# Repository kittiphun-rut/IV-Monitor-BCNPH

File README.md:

# IV-Monitor-BCNPH

ซอฟต์แวร์ของโครงการนวัตกรรม **Smart IV Alert** — ระบบตรวจวัดและแจ้งเตือนการให้สารน้ำทางหลอดเลือดดำ
(หอผู้ป่วยอายุรกรรม โรงพยาบาลสูงเม่น จังหวัดแพร่ / วิทยาลัยพยาบาลบรมราชชนนี แพร่)

## โครงสร้างที่เก็บ

เฟิร์มแวร์เก็บเป็น **โฟลเดอร์ชื่อคงที่สายละหนึ่ง** เลขเวอร์ชันอยู่ใน `#define APP_VERSION`
เวอร์ชันเก่าทุกตัวดูได้จาก [`VERSIONS.md`](VERSIONS.md) ซึ่งมีลิงก์โหลด zip ของทุกรุ่น

| ที่อยู่ | คำอธิบาย |
|---|---|
| `firmware/Station/` | **เฟิร์มแวร์เครื่องประจำเตียง สายหลัก** — ไม่ต้องคาลิเบรตด้วยมือ หนีบเซนเซอร์แล้วเปิดโรลเลอร์ เครื่องเรียนรู้เอง หมุนจอ 180 องศาได้ สุ่มจังหวะส่งข้อมูลกันชนกัน |
| `firmware/Station-Stable/` | **เฟิร์มแวร์เครื่องประจำเตียง สายเสถียร** — อัลกอริทึมตรวจจับเดิมพร้อมหน้าคาลิเบรต ๓ ขั้นแบบทำเอง สำหรับเครื่องที่ยังใช้วิธีเดิม |
| `firmware/Host-OLED/` | **เฟิร์มแวร์เครื่องส่วนกลาง จอ OLED** — ตรวจเลขเตียงซ้ำ หน้า LINK DIAGNOSTIC แอนิเมชันหยด หน้าเว็บ Dashboard |
| `firmware/Host-TFT28/` | **เฟิร์มแวร์เครื่องส่วนกลาง จอสี TFT 2.8"** — หน้าจอแนวทาง FOCUS + จอเตือนเต็มจอ |
| `firmware/Host-Touch24/` | **เฟิร์มแวร์เครื่องส่วนกลาง จอสัมผัส 2.4"** — ตั้งค่าได้บนจอ นาฬิกา DS3231 บันทึกลงการ์ด SD พร้อมคุณสมบัติครบเท่ารุ่นจอ OLED |
| `firmware/FlowSim-Lab/` | **เฟิร์มแวร์แบบจำลองกราฟการไหล + ทดสอบเซนเซอร์** (ไม่เชื่อมต่อ Host) — ใช้ทดลอง สาธิต และออกแบบหน้าจอ |
| `firmware/reference/` | เฟิร์มแวร์ตัวจริงที่ใช้อ้างอิง: Station v7.3.0 / v7.4.0 และ Host v4.6.0 |
| `tools/check-ino-types.py` | ตรวจว่า enum/struct ถูกประกาศก่อนจุดที่ Arduino แทรก prototype (กัน error `does not name a type`) |
| `tools/screen-preview/` | เครื่องมือเรนเดอร์ภาพหน้าจอ TFT จากไฟล์ .ino บนเครื่อง PC |
| `tools/touch-preview/` | เรนเดอร์ภาพหน้าจอของเฟิร์มแวร์ Host จอสัมผัส v4.9.0 บน PC |
| `tools/host-preview/` | เรนเดอร์ภาพหน้าจอ TFT ของเฟิร์มแวร์ Host v4.8.0-TFT บน PC |
| `tools/protocol-test/` | **ตรวจว่าโครงสร้างแพ็กเก็ต ESP-NOW ของทุกเฟิร์มแวร์ตรงกัน** (Host กับ Station ต้องตรงกันทุกไบต์) |
| `tools/oled-check/` | ตรวจว่าเฟิร์มแวร์ Host จอ OLED คอมไพล์ผ่านบน PC |
| `tools/oled-preview/` | **จำลองหน้าจอ OLED 128x64 ของ Host v4.7.4 บน PC** เรนเดอร์ออกมาเป็นภาพทุกหน้า รวมเฟรมแอนิเมชันหยด |
| `tools/host-rx-test/` | **ป้อนแพ็กเก็ตเสมือนเข้าฟังก์ชันรับของ Host บน PC** ตรวจว่า Host มองเห็นครบทุกเตียงจริงหรือไม่ (7 สถานการณ์ รวมกรณีเลขเตียงซ้ำ) |
| `tools/link-sim/` | **จำลองจังหวะเวลาของ ESP-NOW ทั้งระบบ** วัดว่าของเดิมทำให้ Host ขึ้น OFFLINE ผิดพลาดนานเท่าใด และของใหม่แก้ได้แค่ไหน |
| `tools/dashboard-preview/` | **เปิดหน้าเว็บ Dashboard บน PC พร้อมข้อมูลจำลอง** แล้วถ่ายภาพหน้าจอด้วย Chromium |
| `tools/detector-test/` | **ทดสอบอัลกอริทึมตรวจจับหยดบน PC** 10 สถานการณ์ (ถุงแกว่ง ระดับไหล สัญญาณรบกวนแรง ฯลฯ) ไม่ต้องมีบอร์ด |
| `tools/station-preview/` | เรนเดอร์ภาพทุกหน้าจอของเฟิร์มแวร์ Station v7.7.2 บน PC (มีเซนเซอร์จำลองในตัว) |
| `tools/ui-mockup/` | แบบร่าง UI ของจอ Station 3 แนวทาง (เรนเดอร์เป็นภาพเพื่อเลือกแบบก่อนลงมือเขียนจริง) |
| `hardware/` | **ผังการเชื่อมต่ออุปกรณ์ KiCad 7** ของเครื่องประจำเตียงและเครื่องศูนย์กลาง สร้างจากหมายเลขขาในเฟิร์มแวร์โดยอัตโนมัติ พร้อมสคริปต์ตรวจว่าผังตรงกับโค้ด |
| `docs/screens/` | ภาพตัวอย่างหน้าจอที่สร้างจากเครื่องมือข้างต้น |
| `docs/ui-concepts/` | ภาพเปรียบเทียบแบบร่าง UI ทั้ง 3 แนวทาง |
| `docs/screens-touch/` | ภาพหน้าจอจริงของ Host v4.9.1-TOUCH ทุกหน้า |
| `docs/ui-concepts-touch/` | แบบร่าง UI แบบสมาร์ตโฟนที่ใช้ประกอบการเลือก |
| `docs/screens-host/` | ภาพหน้าจอจริงของ Host v4.8.0-TFT ทุกหน้า |
| `docs/ui-concepts-host/` | ภาพเปรียบเทียบแบบร่าง UI ของ Host ทั้ง 3 แนวทาง |
| `docs/screens-dashboard/` | ภาพหน้าเว็บ Dashboard ที่เรนเดอร์จากเบราว์เซอร์จริง |
| `docs/screens-station/` | ภาพหน้าจอจริงของ Station v7.7.2 ทุกหน้า + ภาพเปรียบเทียบจอหมุน 180 องศา |
| `docs/คู่มือพยาบาล_Smart_IV_Alert.docx` | **คู่มือการปฏิบัติงานสำหรับพยาบาลวิชาชีพ** ตามรูปแบบเอกสารราชการไทย ๔๘ หน้า (ปก คำนำ สารบัญ ๗ บท ภาคผนวก ๕ ภาค รวมบทการติดตั้งเซนเซอร์และการคาลิเบรต) — สารบัญเป็นฟิลด์ TOC ที่อัปเดตเองได้ใน Word |
| `docs/คู่มือหน้าเว็บ_Smart_IV_Alert.docx` | **คู่มือการปฏิบัติงานเฉพาะหน้าเว็บ** ๓๐ หน้า อธิบายทุกหน้า ทุกปุ่ม และทุกบรรทัดบนการ์ดเตียง พร้อมภาพถ่ายหน้าจอจริงทั้ง ๔ หน้า |
| `docs/คู่มือพยาบาล_Smart_IV_Alert.txt` | คู่มือฉบับข้อความล้วน สำหรับคัดลอกไปใช้ต่อหรืออ่านโดยไม่ต้องมี Word |
| `docs/คู่มือพยาบาล_Smart_IV_Alert_ตัวอย่าง.pdf` | ตัวอย่าง PDF ของคู่มือ (เรนเดอร์ด้วยฟอนต์แทน ไม่ใช่ TH SarabunPSK) |
| `tools/manual-build/` | **สคริปต์สร้างคู่มือ .docx** สร้างสารบัญเป็นฟิลด์ TOC จริงพร้อมเลขหน้าที่คำนวณไว้ล่วงหน้า |
| `docs/screens-oled/` | ภาพจำลองหน้าจอ OLED ของ Host v4.7.4-OLED ทุกหน้า + เฟรมแอนิเมชันหยด |

## เริ่มต้นที่ไหน

อ่าน [`firmware/FlowSim-Lab/README.md`](firmware/FlowSim-Lab/README.md)
ซึ่งอธิบายผังหน้าจอทั้ง 3 หน้า ตารางปุ่มกด โหมดจำลอง และขั้นตอนคาลิเบรตไว้ครบ

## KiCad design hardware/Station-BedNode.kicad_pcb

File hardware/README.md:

# ผังการเชื่อมต่ออุปกรณ์ (KiCad)

ผังในโฟลเดอร์นี้สร้างด้วย `tools/kicad-gen/gen_schematics.py` ซึ่ง **อ่านหมายเลขขา
GPIO จากไฟล์เฟิร์มแวร์โดยตรง ไม่ได้กรอกด้วยมือ** ถ้าย้ายขาในเฟิร์มแวร์แล้วรันสคริปต์ใหม่
ผังจะตามไปเองทันที ผังกับโค้ดจึงไม่มีทางหลุดจากกัน

```bash
python3 tools/kicad-gen/gen_schematics.py
```

| ไฟล์ | บอร์ด | อ่านขาจาก |
|---|---|---|
| `Station-BedNode.kicad_sch` | เครื่องประจำเตียง v7.7.3 | `firmware/Station/` |
| `Host-OLED.kicad_sch` | เครื่องศูนย์กลาง v4.7.5-OLED | `firmware/Host-OLED/` |

เปิดด้วย KiCad 7 ขึ้นไป (ไฟล์ `.kicad_pro` มีให้แล้ว) นิยามสัญลักษณ์ทั้งหมดฝังอยู่ในไฟล์
จึงเปิดได้บนเครื่องที่ไม่ได้ติดตั้งไลบรารีมาตรฐานของ KiCad

## ทำไมข้อความในผังเป็นภาษาอังกฤษ

KiCad 7 **ไม่รองรับการจัดวางสระและวรรณยุกต์ไทย** ทดสอบแล้วพบว่าเครื่องหมายบนและล่าง
หายทั้งหมด เช่น "อัตราการไหล" เรนเดอร์ออกมาเป็น "อตราการไหล" และ "ผู้ป่วย" เป็น "ผปวย"
ถ้าใส่ภาษาไทยลงไปจะได้เอกสารที่อ่านผิดความหมาย จึงใช้ภาษาอังกฤษในผัง (เป็นธรรมเนียม
ของงาน EDA อยู่แล้ว) และอธิบายภาษาไทยไว้ในไฟล์นี้แทน

## เครื่องประจำเตียง (Station v7.7.3)

| อุปกรณ์ | ขา ESP32-S3 | หมายเหตุ |
|---|---|---|
| จอ TFT ST7789 1.47" — SCLK | GPIO 13 | |
| จอ TFT — MOSI (SDA) | GPIO 12 | |
| จอ TFT — RST | GPIO 11 | |
| จอ TFT — DC | GPIO 10 | |
| จอ TFT — CS | GPIO 9 | |
| จอ TFT — BLK (ไฟหน้าจอ) | GPIO 8 | |
| เซนเซอร์ TCRT5000 — AO | GPIO 4 | ขา DO ไม่ได้ใช้ |
| บัซเซอร์ | GPIO 3 | ชนิด Passive ขับด้วย `tone()` |
| ปุ่มผู้ใช้ | GPIO 2 | ต่อลง GND ได้เลย |
| RGB LED (WS2812) | GPIO 48 | **อยู่บนบอร์ดแล้ว ไม่ต้องต่อเพิ่ม** |

**ข้อควรระวัง**

1. จ่ายไฟจอและเซนเซอร์ด้วย **3V3 เท่านั้น** ขา GPIO ของ ESP32-S3 ทนได้ 3.3V การต่อ 5V
   เข้าขาสัญญาณจะทำให้ชิปเสียหาย
2. ปุ่มใช้ `pinMode(INPUT_PULLUP)` จึงต่อระหว่าง GPIO กับ GND ได้เลย ไม่ต้องมีตัวต้านทาน
   พูลอัปภายนอก
3. บัซเซอร์ที่ใช้ต้องเป็นชนิด **Passive** เพราะเฟิร์มแวร์สร้างความถี่เองด้วย `tone()`
   ถ้าใช้บัซเซอร์แบบแม่เหล็กซึ่งกินกระแสสูง ให้เพิ่มทรานซิสเตอร์ NPN ขับ อย่าต่อตรงกับ GPIO
4. วงจรวัดแบตเตอรี่ฝั่ง Station **ปิดอยู่ในเฟิร์มแวร์** (`STATION_BAT_ADC_PIN = -1`)
   ผังจึงไม่ได้วาดไว้ ถ้าจะเปิดใช้ ต้องแก้ค่านี้เป็นหมายเลขขา ADC แล้วต่อตัวแบ่งแรงดัน 1:1

## เครื่องศูนย์กลาง (Host v4.7.5-OLED)

| อุปกรณ์ | ขา ESP32-S3 | หมายเหตุ |
|---|---|---|
| จอ OLED SH1106 — SDA | GPIO 8 | I2C 400 kHz |
| จอ OLED SH1106 — SCL | GPIO 9 | |
| ปุ่มเปิด-ปิด / พักเสียงเตือน | GPIO 4 | **ต้องเป็น RTC GPIO (0-21)** |
| ปุ่มเปลี่ยนหน้าจอ | GPIO 5 | |
| บัซเซอร์ | GPIO 7 | ชนิด Passive |
| วัดแรงดันแบตเตอรี่ | GPIO 1 | ผ่านตัวแบ่งแรงดัน 1:1 |

**ข้อควรระวัง**

1. ปุ่มเปิด-ปิดต้องอยู่บนขา RTC GPIO เพราะใช้ปลุกเครื่องจาก deep sleep ด้วย `ext0`
   ที่ระดับลอจิก 0 ถ้าย้ายไปขาอื่นที่ไม่ใช่ RTC GPIO เครื่องจะปลุกไม่ขึ้น
2. **R1 กับ R2 ต้องมีค่าเท่ากัน** เฟิร์มแวร์คำนวณ `(raw / 4095) × 3.3 × 2.0`
   ซึ่งตรึงอัตราส่วนไว้ที่ 1:1 แล้ว ถ้าใช้ค่าต่างกันค่าที่อ่านได้จะผิด
   แบตเตอรี่เต็มที่ 4.2V ผ่านตัวแบ่งเหลือ 2.1V ยังอยู่ในช่วงที่ ADC รับได้
3. โมดูล OLED สำเร็จรูปส่วนใหญ่มีตัวต้านทานพูลอัป I2C มาแล้ว ถ้าโมดูลที่ใช้ไม่มี
   ให้เพิ่ม 4.7kΩ จาก SDA ขึ้น 3V3 และ 4.7kΩ จาก SCL ขึ้น 3V3
4. บัสวิ่งที่ 400 kHz ตามสเปก SH1106 ควรให้สายสั้นที่สุดเท่าที่ทำได้

## การตรวจสอบ

ผังทั้งสองผ่านการตรวจด้วย `kicad-cli` เวอร์ชัน 7.0.11 โดยตรวจสองชั้น

1. **เปิดไฟล์ได้จริง** — `kicad-cli sch export pdf` สร้าง PDF สำเร็จทั้งสองไฟล์
2. **การเชื่อมต่อถูกต้อง** — `kicad-cli sch export netlist` แล้วตรวจทุกเน็ตทีละเส้น
   ว่าตรงกับ `#define` ในเฟิร์มแวร์

```bash
kicad-cli sch export pdf     --output Station-BedNode.pdf Station-BedNode.kicad_sch
kicad-cli sch export netlist --output Station-BedNode.net Station-BedNode.kicad_sch
```

## ขอบเขตที่ยังไม่ได้ทำ

* **ยังไม่มีการวางลายวงจร (PCB layout)** ผังนี้เป็นผังการเชื่อมต่ออุปกรณ์ สำหรับต่อสาย
  ระหว่างโมดูลสำเร็จรูปหรือบัดกรีบนเพอร์ฟบอร์ด ยังไม่ได้ออกแบบแผ่นวงจรพิมพ์
* **ยังไม่ได้ประกอบและทดสอบกับฮาร์ดแวร์จริง** ผังสร้างจากการอ่านโค้ด ควรตรวจทานกับ
  ซิลค์สกรีนบนบอร์ดจริงอีกครั้งก่อนบัดกรี
* **ยังไม่มีผังของ Host รุ่นจอ TFT (v4.8.0) และรุ่นจอสัมผัส (v4.9.0)** ทั้งสองรุ่นใช้ผังขา
  ต่างจากรุ่น OLED

---

# แผ่นวงจรพิมพ์ (PCB)

เป็น **บอร์ดรอง (carrier board)** สองชั้น รูทะลุทั้งหมด ไม่มีชิ้นส่วน SMD
โมดูลสำเร็จรูปทุกตัวเสียบลงหัวต่อ จึงบัดกรีด้วยมือได้และถอดเปลี่ยนโมดูลที่เสียได้

```bash
python3 tools/kicad-gen/gen_pcb.py     # สร้างบอร์ดใหม่จากหมายเลขขาในเฟิร์มแวร์
bash hardware/verify_pcb.sh            # รัน DRC จริงแล้วรายงานเฉพาะระดับ error
```

| ไฟล์ | คือ |
|---|---|
| `Station-BedNode.kicad_pcb` | บอร์ดเครื่องประจำเตียง ขนาด ๑๐๐ x ๘๖ มม. |
| `Host-OLED.kicad_pcb` | บอร์ดเครื่องศูนย์กลาง ขนาด ๑๐๐ x ๘๖ มม. |
| `ModuleFitCheck.kicad_pcb` / `.pdf` | **แผ่นทดสอบขนาดโมดูล ๑:๑** |
| `gerbers/<board>/` | ไฟล์สั่งผลิต Gerber + Excellon drill |
| `<board>-PCB.pdf` | ภาพบอร์ดสำหรับดูและตรวจทาน |

## ⚠ ต้องทำก่อนสั่งผลิต — ตรวจขนาดโมดูลด้วยแผ่น ๑:๑

บอร์ด ESP32-S3 Super Mini เป็นบอร์ดที่ผู้ผลิตแต่ละเจ้าทำไม่เหมือนกัน ทั้ง **จำนวนขาต่อแถว
ระยะห่างระหว่างสองแถว และลำดับว่าขาไหนคือ GPIO อะไร** ค่าที่ใช้อยู่ตอนนี้เป็นค่าตั้งต้น
ที่ **ยังไม่ได้ยืนยันกับบอร์ดจริง** ถ้าไม่ตรง บอร์ดที่สั่งมาจะเสียบโมดูลไม่ลงและใช้ไม่ได้เลย

ขั้นตอนตรวจ

1. พิมพ์ `ModuleFitCheck.pdf` โดยตั้งค่าเครื่องพิมพ์เป็น **สเกล ๑๐๐% หรือ Actual size**
   ห้ามใช้ Fit to page
2. **วัดแถบ ๑๐ มม. บนกระดาษด้วยไม้บรรทัดก่อน** ถ้าไม่ได้ ๑๐ มม. พอดี แปลว่าตั้งค่าพิมพ์ผิด
   อย่าเพิ่งใช้แผ่นนี้ตัดสิน
3. วางบอร์ด ESP32-S3 Super Mini ตัวจริงทาบลงบนรอยขาสองแถว ขาต้องลงรูพอดีทุกขา
4. เทียบชื่อ GPIO ที่พิมพ์ไว้กับซิลค์สกรีนบนโมดูลจริงทีละขา
5. ถ้าไม่ตรง ให้แก้ `MODULE` ที่หัวไฟล์ `tools/kicad-gen/gen_pcb.py` แล้วรันใหม่

```python
MODULE = dict(
    rows=8,                 # จำนวนขาต่อหนึ่งแถว
    row_pitch=15.24,        # ระยะห่างระหว่างสองแถว (มม.)
    pin_pitch=2.54,         # ระยะห่างระหว่างขาในแถวเดียวกัน (มม.)
    left=['5V', 'GND', '3V3', 'GPIO13', 'GPIO12', 'GPIO11', 'GPIO10', 'GPIO9'],
    right=['GPIO8', 'GPIO7', 'GPIO6', 'GPIO5', 'GPIO4', 'GPIO3', 'GPIO2', 'GPIO1'],
)
MODULE_VERIFIED = False     # ตั้งเป็น True เมื่อตรวจกับบอร์ดจริงแล้ว
```

ตราบใดที่ `MODULE_VERIFIED` ยังเป็น `False` บอร์ดจะพิมพ์คำเตือน
`MODULE FOOTPRINT UNVERIFIED` ไว้บนซิลค์สกรีน เพื่อกันการสั่งผลิตโดยยังไม่ได้ตรวจ

## วิธีเดินลายที่ใช้

เดินแบบ **แมนฮัตตันสองชั้น** — `F.Cu` เดินเฉพาะแนวตั้ง `B.Cu` เดินเฉพาะแนวนอน ต่อกันด้วยเวีย
ตัวสร้างบังคับเงื่อนไขสามข้อด้วยโค้ดก่อนเดินสายทุกครั้ง ถ้าข้อใดไม่ผ่านจะหยุดทันที

1. ขาที่ต้องเดินสายทุกขาบนฝั่งเดียวกันต้องห่างกันในแนว y อย่างน้อย ๑.๐ มม.
2. ทุกเส้นได้คอลัมน์ x ของตัวเอง
3. คอลัมน์ต้องอยู่ในช่องเดินสายที่ไม่มีขาอุปกรณ์

เมื่อครบสามข้อ ลายจะไม่มีทางทับกันเลยโดยโครงสร้าง ไม่ต้องพึ่งการตรวจด้วยสายตา

ลายกว้าง ๐.๔ มม. ระยะห่าง ๐.๒๕ มม. เวีย ๐.๘ มม. เจาะ ๐.๔ มม.
ค่าเหล่านี้อยู่ในเกณฑ์ที่โรงงาน PCB ราคาประหยัดทุกเจ้ารับผลิตได้

## ผลตรวจ

รัน DRC จริงผ่าน `pcbnew.WriteDRCReport()` ของ KiCad 7.0.11

| บอร์ด | error | unconnected pads | warning |
|---|---|---|---|
| Station-BedNode | **๐** | **๐** | ๑๗ |
| Host-OLED | **๐** | **๐** | ๑๙ |

warning ที่เหลือเป็นเรื่องซิลค์สกรีนซ้อนทับกันเล็กน้อย และ `lib_footprint_issues`
ซึ่งเกิดจากการโหลด footprint จากพาธไฟล์โดยตรงแทนที่จะผ่านตารางไลบรารี ทั้งสองอย่าง
ไม่กระทบการผลิตและไม่กระทบการทำงานทางไฟฟ้า

## ขอบเขตที่ยังไม่ได้ทำ

* **ยังไม่ได้สั่งผลิตและยังไม่ได้ประกอบจริง** ทุกอย่างตรวจด้วยเครื่องมือบนเครื่องเท่านั้น
* **ขนาดและผังขาของโมดูล ESP32-S3 Super Mini ยังไม่ได้ยืนยัน** ดูหัวข้อด้านบน
* ยังไม่ได้ออกแบบกล่อง ตำแหน่งรูยึด M3 ทั้งสี่มุมกำหนดไว้ห่างขอบ ๔ มม.
  ควรตรวจกับกล่องจริงก่อน
* ยังไม่มีบอร์ดของ Host รุ่นจอ TFT v4.8.0 และรุ่นจอสัมผัส v4.9.0

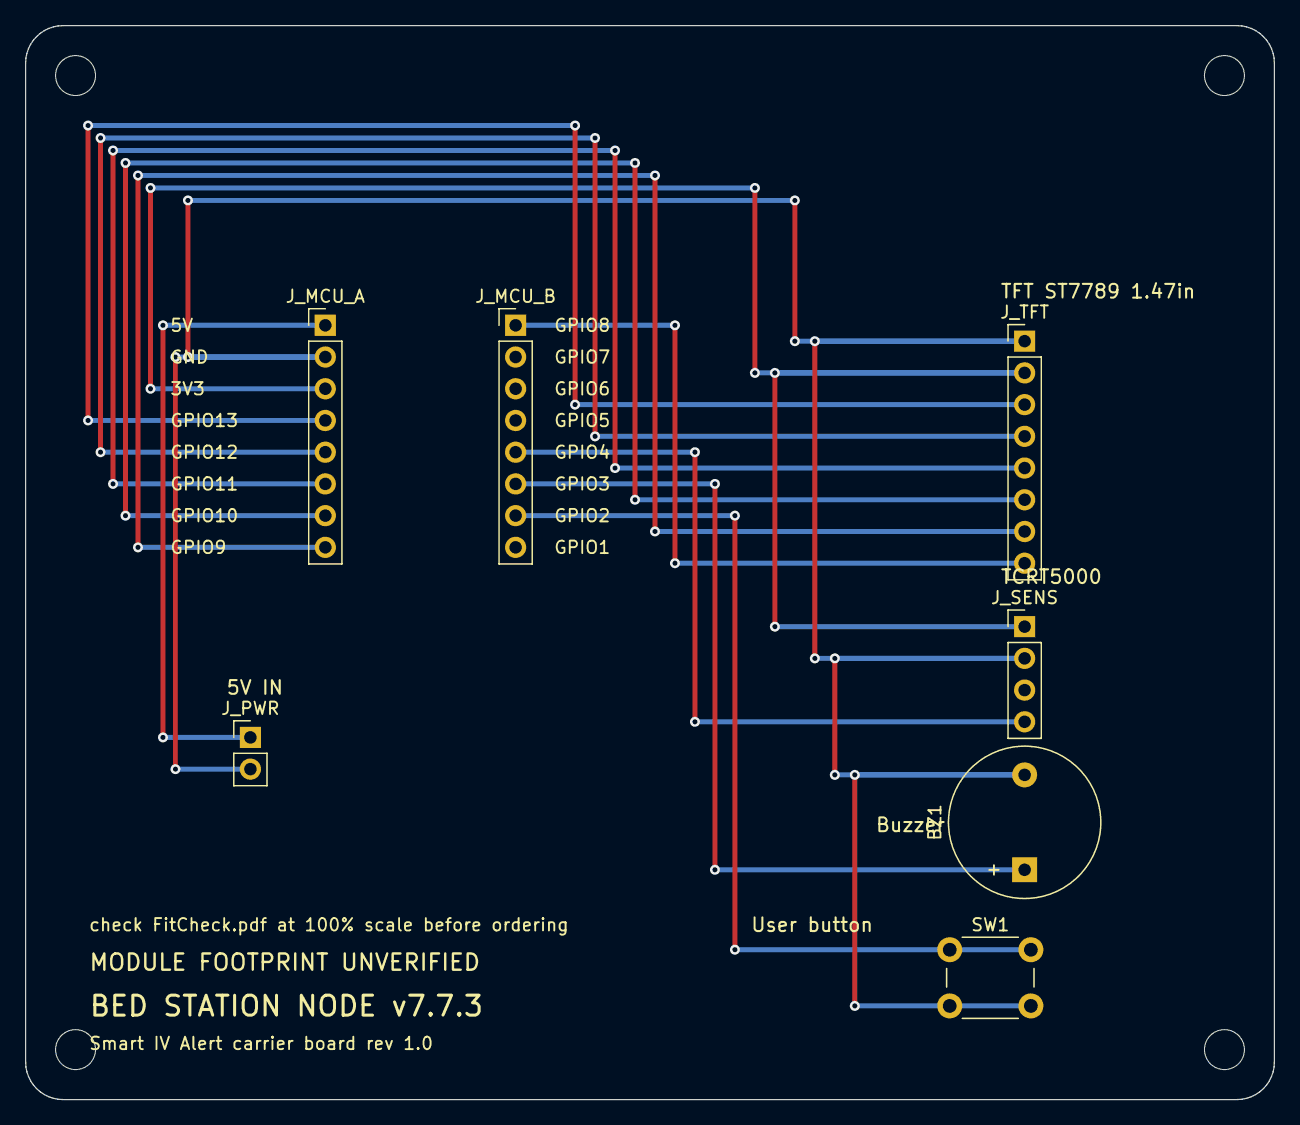
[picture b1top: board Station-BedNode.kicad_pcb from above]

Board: 2 copper layers, 100.0 x 86.0 mm, 11 parts (0 on the bottom side), 12 nets.

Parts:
BZ1: Buzzer; Buzzer_12x9.5RM7.6
H1, H2, H3, H4: MountingHole_3.2mm_M3
J_MCU_A: ESP32-S3 row A; PinHeader_1x08_P2.54mm_Vertical
J_MCU_B: ESP32-S3 row B; PinHeader_1x08_P2.54mm_Vertical
J_PWR: 5V IN; PinHeader_1x02_P2.54mm_Vertical
J_SENS: TCRT5000; PinHeader_1x04_P2.54mm_Vertical
J_TFT: TFT ST7789 1.47in; PinHeader_1x08_P2.54mm_Vertical
SW1: User button; SW_PUSH_6mm

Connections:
+3V3: J_MCU_A.3, J_SENS.1, J_TFT.2
+5V: J_MCU_A.1, J_PWR.1
BTN: J_MCU_B.7, SW1.1
BUZZER: BZ1.1, J_MCU_B.6
DROP_AO: J_MCU_B.5, J_SENS.4
GND: BZ1.2, J_MCU_A.2, J_PWR.2, J_SENS.2, J_TFT.1, SW1.2
TFT_BLK: J_MCU_B.1, J_TFT.8
TFT_CS: J_MCU_A.8, J_TFT.7
TFT_DC: J_MCU_A.7, J_TFT.6
TFT_MOSI: J_MCU_A.5, J_TFT.4
TFT_RST: J_MCU_A.6, J_TFT.5
TFT_SCLK: J_MCU_A.4, J_TFT.3

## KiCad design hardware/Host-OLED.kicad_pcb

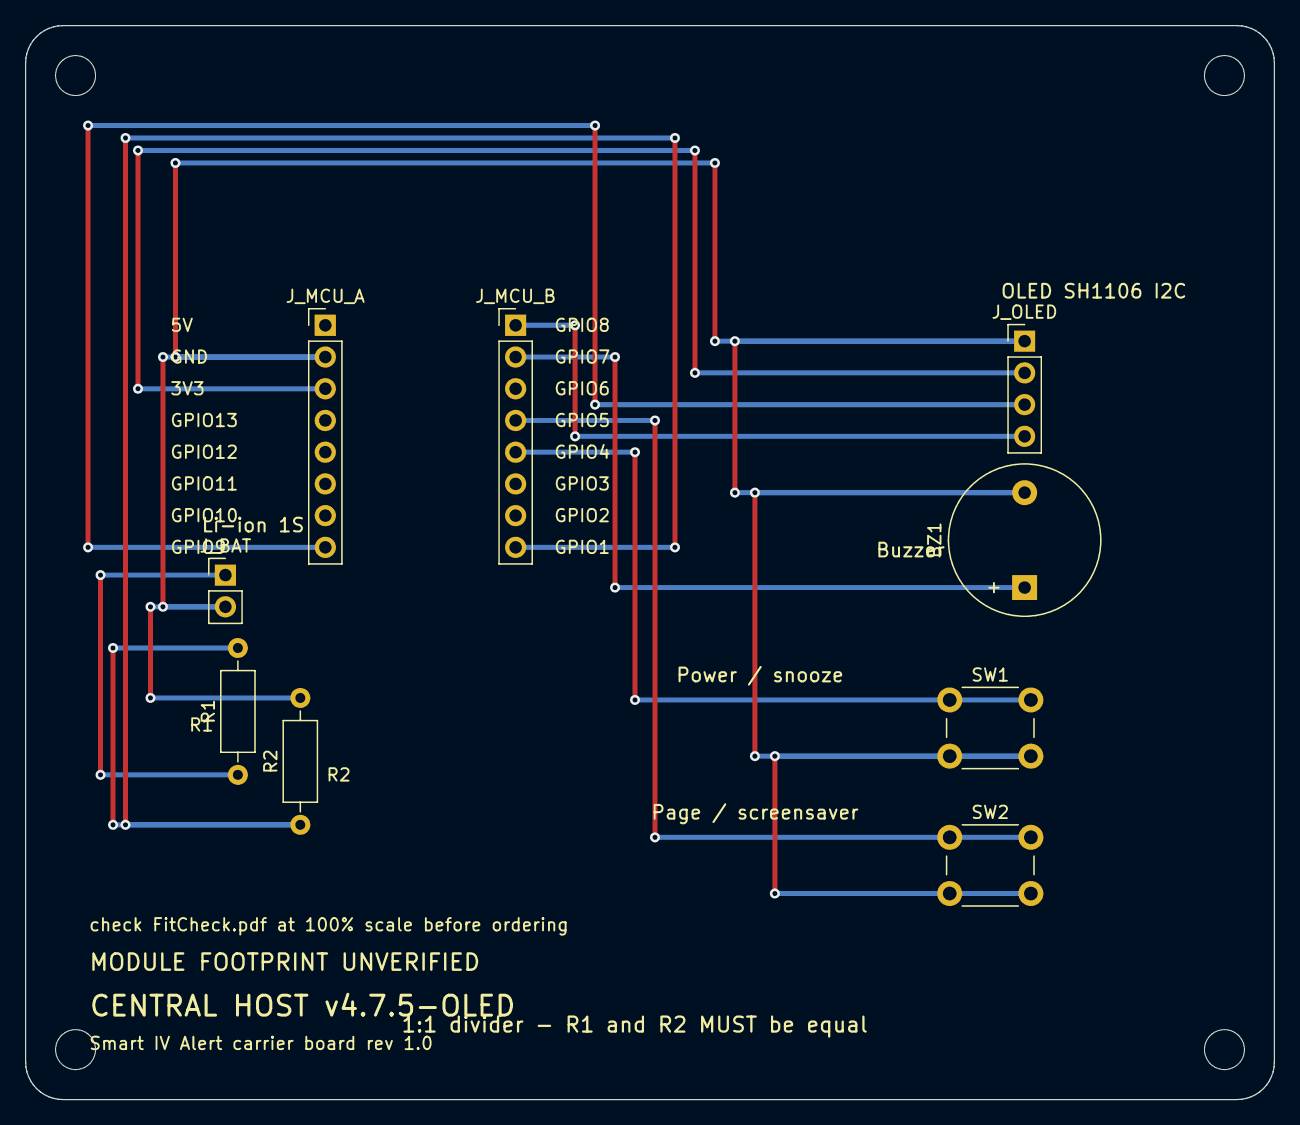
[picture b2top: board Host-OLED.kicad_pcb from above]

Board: 2 copper layers, 100.0 x 86.0 mm, 13 parts (0 on the bottom side), 9 nets.

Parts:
BZ1: Buzzer; Buzzer_12x9.5RM7.6
H1, H2, H3, H4: MountingHole_3.2mm_M3
J_BAT: Li-ion 1S; PinHeader_1x02_P2.54mm_Vertical
J_MCU_A: ESP32-S3 row A; PinHeader_1x08_P2.54mm_Vertical
J_MCU_B: ESP32-S3 row B; PinHeader_1x08_P2.54mm_Vertical
J_OLED: OLED SH1106 I2C; PinHeader_1x04_P2.54mm_Vertical
R1, R2: 100k; R_Axial_DIN0207_L6.3mm_D2.5mm_P10.16mm_Horizontal
SW1: Power/snooze; SW_PUSH_6mm
SW2: Page; SW_PUSH_6mm

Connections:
+3V3: J_MCU_A.3, J_OLED.2
BTN_PAGE: J_MCU_B.4, SW2.1
BTN_POWER: J_MCU_B.5, SW1.1
BUZZER: BZ1.1, J_MCU_B.2
GND: BZ1.2, J_BAT.2, J_MCU_A.2, J_OLED.1, R2.2, SW1.2, SW2.2
OLED_SCL: J_MCU_A.8, J_OLED.3
OLED_SDA: J_MCU_B.1, J_OLED.4
VBAT+: J_BAT.1, R1.1
VBAT_SENSE: J_MCU_B.8, R1.2, R2.1

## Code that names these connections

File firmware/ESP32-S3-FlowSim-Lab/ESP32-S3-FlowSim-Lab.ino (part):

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 *  [2] TREND  — กราฟแท่งแนวโน้มอัตราไหล (gtt/min) ย้อนหลัง 60 วินาที
 *  [3] SENSOR — ค่าคาลิเบรต, เกจตำแหน่งสัญญาณ, สัญญาณรบกวน และคะแนนความไว
 *
 * ปุ่มกดเดียว (BTN_PIN) ทำได้ทุกคำสั่ง
 *  1 คลิก  = เปลี่ยนหน้า            2 คลิก  = RUN / HOLD (หยุดพักการนับ)
 *  3 คลิก  = ล้างสถิติทั้งหมด        4 คลิก  = เปิด/ปิดโหมดจำลองและเลือกอัตรา
 *  กด 3 วิ = เข้า Calibration Wizard  กด 5 วิ = หน้าวิธีใช้/ผู้พัฒนา
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// ----------------------------------------------------------------------------
// ขาต่อใช้งาน (เหมือนเครื่องจริงทุกประการ เพื่อให้ย้ายโค้ดกลับไปใช้ได้ทันที)
// ----------------------------------------------------------------------------
#define TFT_CS        9
#define TFT_DC        10
#define TFT_RST       11
#define TFT_MOSI      12
#define TFT_SCLK      13
#define TFT_BLK       8

#define SENSOR_AO_PIN 4
#define BUZZER_PIN    3
#define BTN_PIN       2
#define RGB_LED_PIN   48

// ----------------------------------------------------------------------------
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}

void beepNonBlocking(uint16_t freq, uint16_t durationMs) {
  tone(BUZZER_PIN, freq);
  buzzerBeepUntil = millis() + durationMs;
}

void modalSafeBeep(uint16_t freq, uint16_t durationMs) {
  tone(BUZZER_PIN, freq);
  delay(durationMs);
  noTone(BUZZER_PIN);
  buzzerBeepUntil = 0;
}

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
void handleBuzzerEngine(unsigned long now) {
  if (buzzerBeepUntil > 0 && now >= buzzerBeepUntil) {
    noTone(BUZZER_PIN);
    buzzerBeepUntil = 0;
  }
}
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
// รอผู้ใช้กดปุ่มพร้อมแสดงค่า ADC สดและช่วงแกว่ง เพื่อให้ตั้งตำแหน่งเซนเซอร์ได้นิ่งก่อนเก็บค่า
int waitAndMonitorSensorStep(const char* stepTitle, const char* stepDescTh, const char* stepDescEn, uint16_t boxColor) {
  noTone(BUZZER_PIN);
  buzzerBeepUntil = 0;

  tft.fillRoundRect(6, 36, 160, 152, 8, THEME_DARKBOX);
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  unsigned long lastAdcUpdate = 0, winStart = millis();
  int lastVal = -1, wMin = 4095, wMax = 0, shownSpread = -1;

  while (digitalRead(BTN_PIN) == HIGH) {
    int liveAdc = analogRead(SENSOR_AO_PIN);
    if (liveAdc < wMin) wMin = liveAdc;
    if (liveAdc > wMax) wMax = liveAdc;
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  }

  modalSafeBeep(2400, 40);
  while (digitalRead(BTN_PIN) == LOW) delay(10);
  delay(60);

  tft.fillRect(20, 102, 132, 44, THEME_NAVY);
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}

void executeCalibrationWizard() {
  noTone(BUZZER_PIN);
  buzzerBeepUntil = 0;

  tft.fillScreen(THEME_BG);
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  static int clickCount = 0;
  static unsigned long lastReleaseTime = 0;

  bool reading = (digitalRead(BTN_PIN) == LOW);
  unsigned long now = millis();

  if (reading && !isHolding) {
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void setup() {
  Serial.begin(115200);

  pinMode(BUZZER_PIN, OUTPUT); noTone(BUZZER_PIN);
  pinMode(TFT_BLK, OUTPUT); digitalWrite(TFT_BLK, HIGH);
  pinMode(BTN_PIN, INPUT_PULLUP);
  pinMode(SENSOR_AO_PIN, INPUT);

  analogReadResolution(12);
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
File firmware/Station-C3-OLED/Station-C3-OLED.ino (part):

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// ---------------------------------------------------------------------------
#define SENSOR_AO_PIN       4
#define BAT_ADC_PIN         0
#define BUZZER_PIN          3
#define BUTTON_PIN          7
#define OLED_SCL_PIN        6
#define OLED_SDA_PIN        5

// ---------------------------------------------------------------------------
// ค่าคงที่ของระบบ (ให้ตรงกับสายหลัก จะได้ประพฤติเหมือนกัน)
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// อุปกรณ์
// ---------------------------------------------------------------------------
U8G2_SSD1306_72X40_ER_F_HW_I2C u8g2(U8G2_R0, /* reset=*/ U8X8_PIN_NONE,
                                    /* clock=*/ OLED_SCL_PIN, /* data=*/ OLED_SDA_PIN);
Preferences stationPrefs;
iv::DropDetector detector;

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}

void serviceBeep(unsigned long now) {
  if (beepRemaining == 0 && !beepIsOn) { digitalWrite(BUZZER_PIN, LOW); return; }
  if (now < beepNextChange) return;

  if (!beepIsOn) {
    if (beepRemaining == 0) { digitalWrite(BUZZER_PIN, LOW); return; }
    digitalWrite(BUZZER_PIN, HIGH);
    beepIsOn = true;
    beepNextChange = now + beepOnMs;
  } else {
    digitalWrite(BUZZER_PIN, LOW);
    beepIsOn = false;
    beepRemaining--;
    beepNextChange = now + beepOffMs;
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  pinMode(SENSOR_AO_PIN, INPUT);
  pinMode(BAT_ADC_PIN,   INPUT);
  pinMode(BUTTON_PIN,    INPUT_PULLUP);
  pinMode(BUZZER_PIN,    OUTPUT);
  digitalWrite(BUZZER_PIN, LOW);

  analogReadResolution(12);
  analogSetAttenuation(ADC_11db);
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  totalDrops    = tallyRestore(stationId);
  totalVolumeMl = (float)totalDrops / (float)safeDropFactor(dropFactor);

  Wire.begin(OLED_SDA_PIN, OLED_SCL_PIN);
  u8g2.begin();
  drawSplash();
  beepPattern(2, 40, 45);
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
